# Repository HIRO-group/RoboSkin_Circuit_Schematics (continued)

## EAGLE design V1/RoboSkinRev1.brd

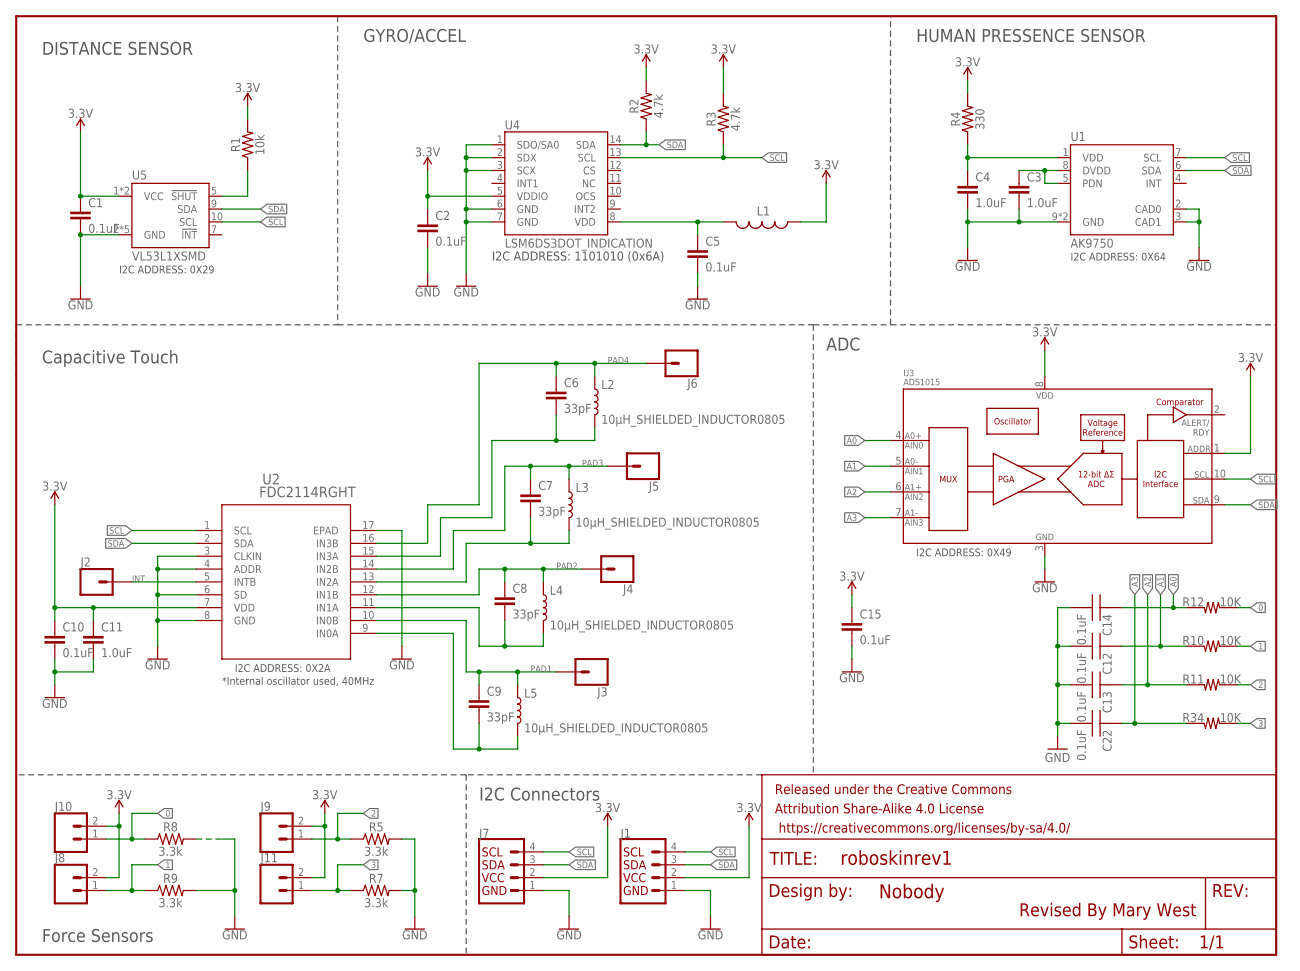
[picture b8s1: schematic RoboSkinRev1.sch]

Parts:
C1, C2, C5, C10, C15: 0.1uF; 0603
C3, C4, C11: 1.0uF; 0603
C6, C7, C8, C9: 33pF; 0603
C12, C13, C14, C22: 0.1uF; 0603_SILK; PARTNO GRM188R70J104KA01D
FRAME1: FRAME-LETTERNO_PACKAGE; DUMMY
J1, J7: QWIIC_CONNECTORJS-1MM; 1X04_1MM_RA
J2, J3, J4, J5, J6: CONN_01; 1X01
J8, J9, J10, J11: CONN_02; 1X02
L1: RES-07859; 0603
L2, L3, L4, L5: 10μH_SHIELDED_INDUCTOR0805; 0805
R1: 10k; 0603
R2, R3: 4.7k; 0603
R4: 330; 0603
R5, R7, R8, R9: 3.3k; 0603
R10, R11, R12, R34: 10K; 0603_SILK; PARTNO CR0603-FX-1002ELF
U1: AK9750; SON10
U2: FDC2114RGHT; RGH16
U3: ADS1015; MSOP10
U4: LSM6DS3DOT_INDICATION; LGA14L_DOT_INDICATOR
U5: VL53L1XSMD; VL53L1X

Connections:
0: J10.1, R8.1, R12.P2 (2)
1: J8.1, R9.1, R10.P2 (2)
2: J9.1, R5.1, R11.P2 (2)
3: J11.1, R7.1, R34.P2 (2)
3.3V: C1.1, C2.1, C10.1, C11.1, C15.1, J1.2 (VCC), J7.2 (VCC), J8.2, J9.2, J10.2, J11.2, L1.1, R1.2, R2.2, R3.2, R4.2, U2.7 (VDD), U3.1 (ADDR), U3.8 (VDD), U4.5 (VDDIO), U5.1 (VCC), U5.11 (VCC)
A0: C14.P1 (1), R12.P1 (1), U3.4 (AIN0)
A1: C12.P1 (1), R10.P1 (1), U3.5 (AIN1)
A2: C13.P1 (1), R11.P1 (1), U3.6 (AIN2)
A3: C22.P1 (1), R34.P1 (1), U3.7 (AIN3)
GND: C1.2, C2.2, C3.2, C4.2, C5.2, C10.2, C11.2, C12.P2 (2), C13.P2 (2), C14.P2 (2), C15.2, C22.P2 (2), J1.1 (GND), J7.1 (GND), R5.2, R7.2, R8.2, R9.2, U1.2 (CAD0), U1.3 (CAD1), U1.9 (GND), U1.10 (GND), U2.3 (CLKIN), U2.4 (ADDR), U2.6 (SD), U2.8 (GND), U2.17 (EPAD), U3.3 (VSS), U4.1 (SDO/SA0), U4.2 (SDX), U4.3 (SCX), U4.6 (GND), U4.7 (GND), U5.2 (GND), U5.3 (GND), U5.4 (GND), U5.6 (GND), U5.12 (GND)
INT: J2.1, U2.5 (INTB)
unnamed: C4.1, R4.1, U1.1 (VDD)
unnamed: C3.1, U1.5 (PDN), U1.8 (DVDD)
unnamed: R1.1, U5.5 (!SHUT)
unnamed: C5.1, L1.2, U4.8 (VDD)
unnamed: C6.2, L2.2, U2.15 (IN3A)
unnamed: C7.2, L3.2, U2.13 (IN2A)
unnamed: C8.2, L4.2, U2.11 (IN1A)
unnamed: C9.2, L5.2, U2.9 (IN0A)
PAD1: C9.1, J3.1, L5.1, U2.10 (IN0B)
PAD2: C8.1, J4.1, L4.1, U2.12 (IN1B)
PAD3: C7.1, J5.1, L3.1, U2.14 (IN2B)
PAD4: C6.1, J6.1, L2.1, U2.16 (IN3B)
SCL: J1.4 (SCL), J7.4 (SCL), R3.1, U1.7 (SCL), U2.1 (SCL), U3.10 (SCL), U4.13 (SCL), U5.10 (SCL)
SDA: J1.3 (SDA), J7.3 (SDA), R2.1, U1.6 (SDA), U2.2 (SDA), U3.9 (SDA), U4.14 (SDA), U5.9 (SDA)

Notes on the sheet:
I2C ADDRESS: 1101010 (0x6A)
Revised By Mary West
I2C ADDRESS: 0X29
I2C ADDRESS: 0X64
HUMAN PRESSENCE SENSOR
GYRO/ACCEL
DISTANCE SENSOR
Capacitive Touch
I2C ADDRESS: 0X2A
*Internal oscillator used, 40MHz
I2C ADDRESS: 0X49
I2C Connectors
Force Sensors
ADC

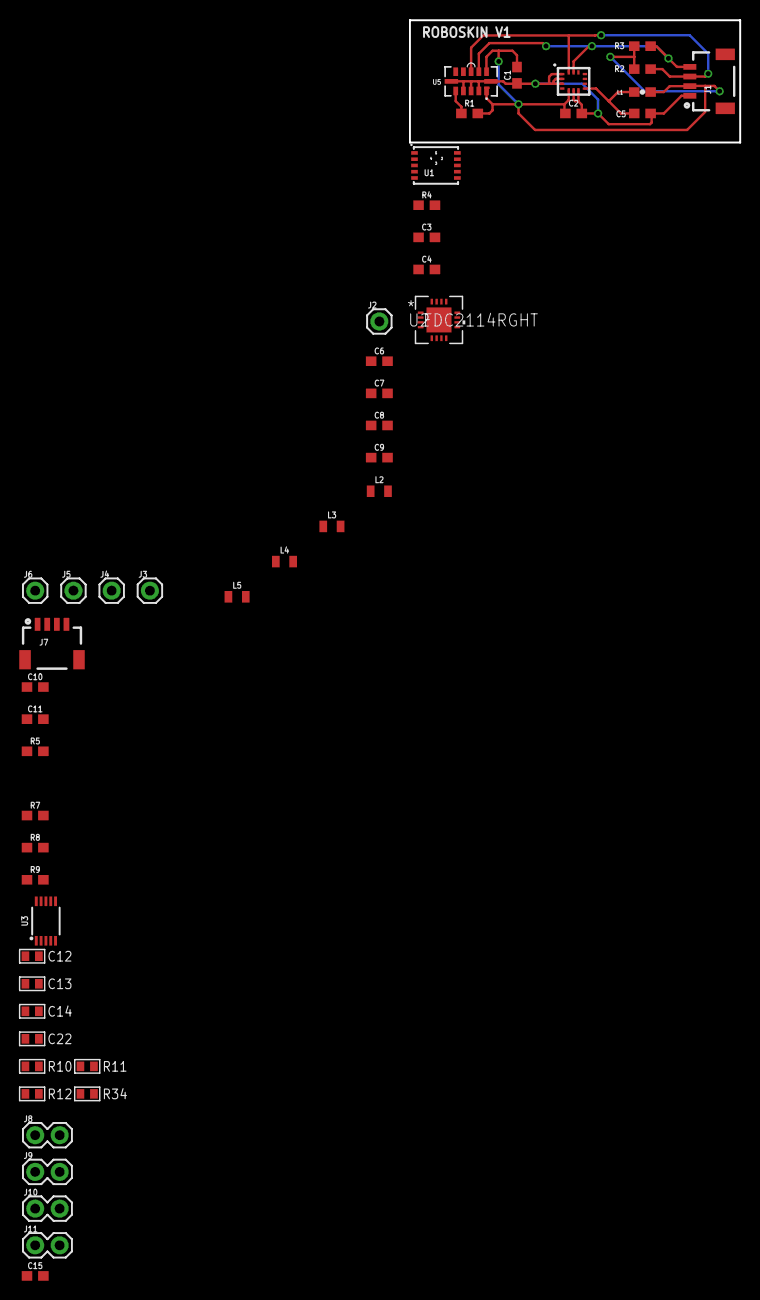
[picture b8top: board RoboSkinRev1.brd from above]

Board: 2 copper layers, 34.3 x 12.7 mm, 51 parts (1 on the bottom side), 25 nets.

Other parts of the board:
U$1: CAPTURE#PNG

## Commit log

2020-02-17 Pushing latest Gerber Files
2020-02-17 Updated Gitignore
2020-02-17 Added Eagle Libraries
2020-02-18 Add schematic to Readme
2020-02-18 change space encoding
2020-02-18 Remove eagle epf
2020-02-18 Update Gerber Files
2020-02-19 Temporary Stable Commit
2020-02-19 Removed old images
2020-02-20 New Circuit
2020-02-20 Kandai Changes in circuit
2020-02-21 Increased spacing
2020-02-21 Kandai Changes
2020-03-10 New Skin Circuit
2020-03-11 Push Latest Changes to Git
2020-03-12 fixed wiring
2020-04-04 Small Update in schematics
2020-05-17 Updated roboskin sensors
2020-05-20 Organizing files into version folders
2020-05-26 Updated schematics with new sensors and supporting circuitry
2020-06-03 NEw PCB formfactor with added circuits, adding BOM, adding PVF
2020-06-27 Adding design files, gerbers, BOM
2020-07-13 adding distance and IMU with WiFi capabilties
2020-07-14 adding BOM and Gerber files
2020-07-14 deleting unnecessary files
2020-07-14 organizing folders
2021-06-13 updating v2 with new accelerometer and adding a power switch
2021-11-30 All versions of hardware
2021-12-01 updated MTCH6301 breakout board because of out of stock parts
